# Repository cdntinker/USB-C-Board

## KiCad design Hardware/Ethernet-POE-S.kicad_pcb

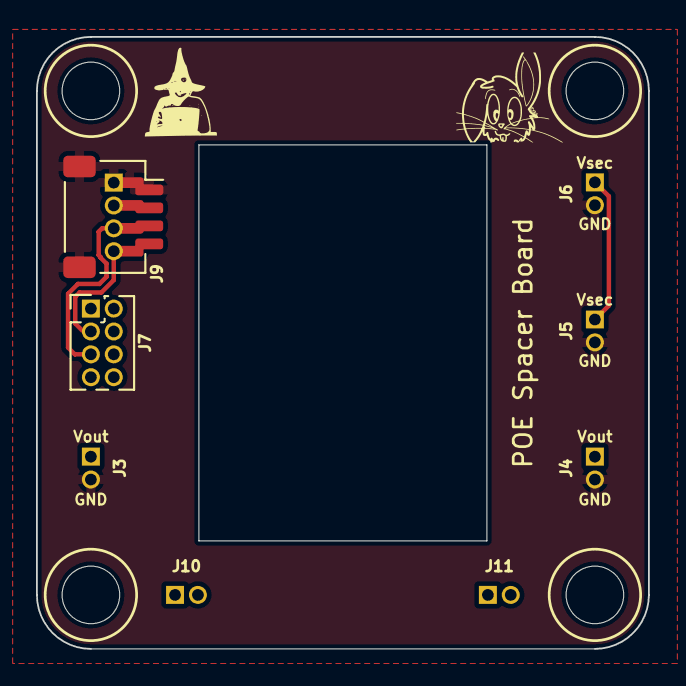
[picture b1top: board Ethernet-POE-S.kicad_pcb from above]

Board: 2 copper layers, 34.0 x 34.0 mm, 8 parts (0 on the bottom side), 4 nets.

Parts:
J3, J4, J5, J6, J10, J11: Conn_01x02_Male; Board_Stacker_2
J7: Conn_01x08_Male; PinHeader_2x04_P1.27mm_Vertical
J9: QWIIC_Stackable; QWIIC_Stack_II

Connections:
GND: J3.2, J4.2, J5.2, J6.2, J9.1, J9.MP (MountPin)
SCL: J7.3, J9.4
SDA: J7.5, J9.3
Vsec: J5.1, J6.1

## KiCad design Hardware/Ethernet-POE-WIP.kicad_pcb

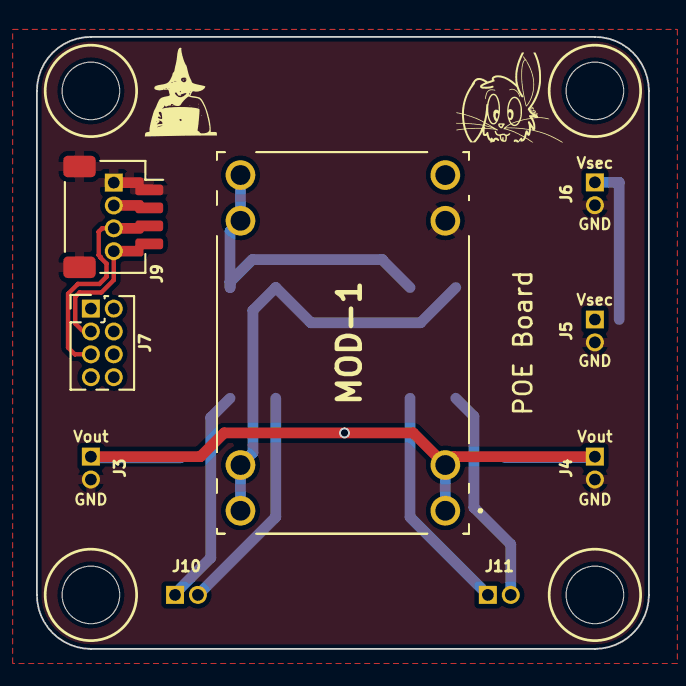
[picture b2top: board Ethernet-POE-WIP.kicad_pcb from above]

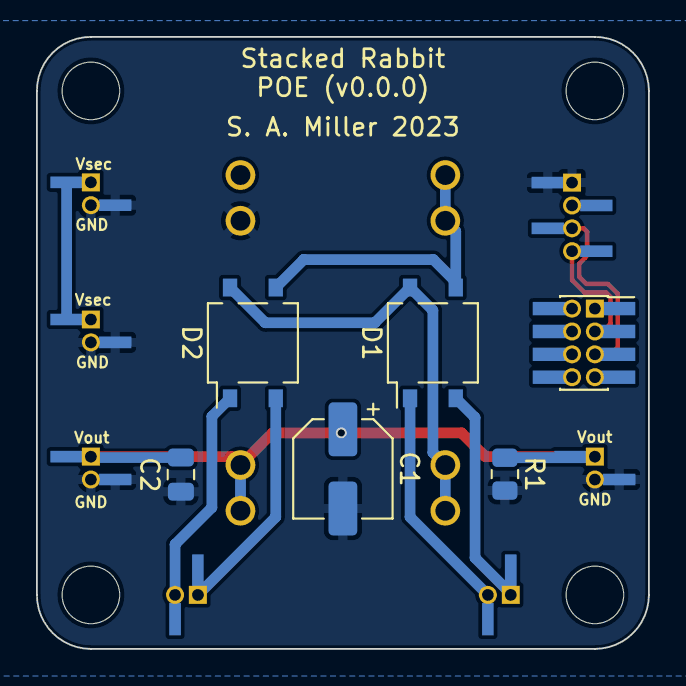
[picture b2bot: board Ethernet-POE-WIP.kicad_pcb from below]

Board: 2 copper layers, 34.0 x 34.0 mm, 14 parts (5 on the bottom side), 11 nets.

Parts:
C1: 100uf; CP_Elec_5x3
C2: 10uf; C_0805_2012Metric
D1, D2: MB4S; TO-269AA
J3, J4, J5, J6, J10, J11: Conn_01x02_Male; Board_Stacker_2
J7: Conn_01x08_Male; PinHeader_2x04_P1.27mm_Vertical
J9: QWIIC_Stackable; QWIIC_Stack_II
MOD-1: Ag9912LP
R1: R; R_0805_2012Metric

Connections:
GND: C1.2, C2.2, J3.2, J4.2, J5.2, J6.2, J9.1, J9.MP (MountPin), MOD-1.3 (-VDC), R1.2
SCL: J7.3, J9.4
SDA: J7.5, J9.3
VA1: D2.2, J11.1
VA2: D2.1, J11.2
VB1: D1.2, J10.1
VB2: D1.1, J10.2
Vin+: D1.3 (+), D2.3 (+), MOD-1.5 (VIN+_1), MOD-1.6 (VIN+_2)
Vin-: D1.4 (-), D2.4 (-), MOD-1.7 (VIN-_1), MOD-1.8 (VIN-_2)
Vout: C1.1, C2.1, J3.1, J4.1, MOD-1.1 (+VDC_1), MOD-1.2 (+VDC_2), R1.1
Vsec: J5.1, J6.1

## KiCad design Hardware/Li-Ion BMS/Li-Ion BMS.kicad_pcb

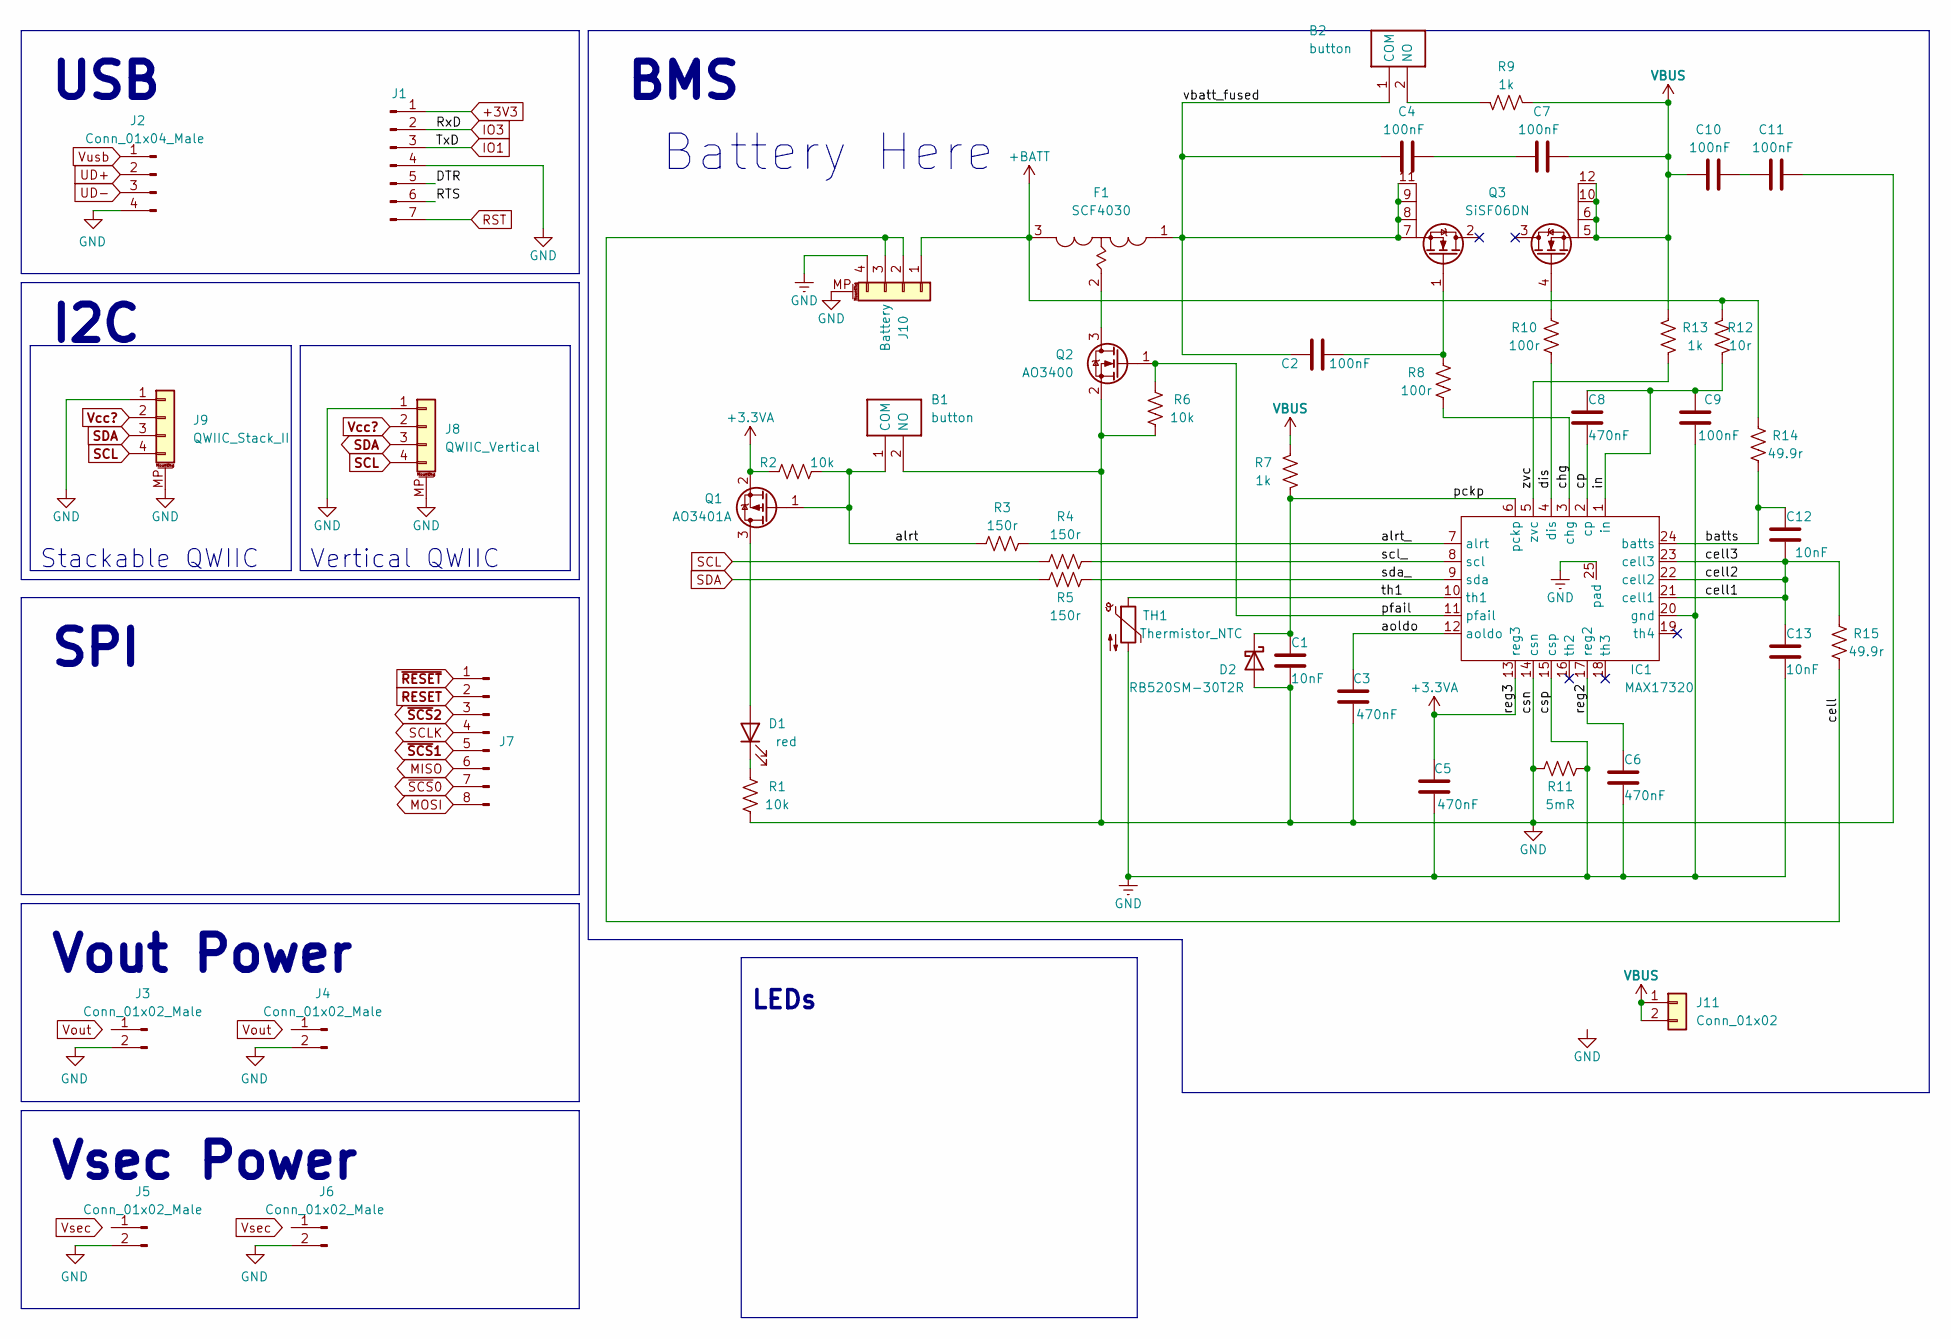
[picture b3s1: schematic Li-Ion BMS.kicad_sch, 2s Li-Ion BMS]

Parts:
B1, B2: button; SW_Push_TS273014TP; LCSC C410373
C1, C12, C13: 10nF; R_0603_1608Metric; LCSC C107059
C2: 100nF; R_0603_1608Metric
C3, C5, C6, C8: 470nF; R_0603_1608Metric; LCSC C1704
C4, C7, C9, C10, C11: 100nF; R_0603_1608Metric; LCSC C83060
D1: red; LED_0603_1608Metric; LCSC C72038
D2: RB520SM-30T2R; D_SOD-523; LCSC C123011
F1: SCF4030; SCF40301204; mouser 504-SCF4030-12-05
IC1: MAX17320; QFN-24-1EP_4x4mm_P0.5mm_EP2.6x2.6mm; mouser 700-MAX17320G20+T
J1: Conn_01x07_Male; Board_Stacker_7
J2: Conn_01x04_Male; Board_Stacker_4; LCSC C2938401 + C2881513
J3, J4, J5, J6: Conn_01x02_Male; Board_Stacker_2; LCSC C2938400 + C2881511
J7: Conn_01x08_Male; PinHeader_2x04_P1.27mm_Vertical; LCSC C2881786 + C2684732
J8: QWIIC_Vertical; LCSC C145961
J9: QWIIC_Stack_II; LCSC C145956 + C2938401 + C2881513
J10: Battery; JST_GH_SM04B-GHS-TB_1x04-1MP_P1.25mm_Horizontal; LCSC C225113
J11: Conn_01x02; PinHeader_1x02_P1.27mm_Vertical
Q1: AO3401A; SOT-23; LCSC C347476
Q2: AO3400; SOT-23; LCSC C20917
Q3: SiSF06DN; SISF06DNT1GE3; mouser 78-SISF06DN-T1-GE3
R1, R2, R6: 10k; R_0603_1608Metric; LCSC C98220
R3, R4, R5: 150r; R_0603_1608Metric; LCSC C22808
R7, R9, R13: 1k; R_0603_1608Metric; LCSC C21190
R8, R10: 100r; R_0603_1608Metric; LCSC C22775
R11: 5mR; R_2512_6332Metric; LCSC C1021512
R12: 10r; R_0603_1608Metric; LCSC C22859
R14, R15: 49.9r; R_0603_1608Metric; LCSC C103679
TH1: Thermistor_NTC; R_0603_1608Metric; LCSC C13564

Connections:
+3.3VA: C5.1, IC1.13 (reg3), Q1.2 (S), R2.1
+BATT: F1.3, J10.1, R12.1, R14.1; also elsewhere on the board
/alrt: B1.1 (COM), Q1.1 (G), R2.2, R3.1
/alrt_: IC1.7 (alrt), R3.2
/aoldo: C3.1, IC1.12 (aoldo)
/chg: IC1.3 (chg), R8.1
/cp: C8.2, IC1.2 (cp)
/dis: IC1.4 (dis), R10.1
/in: C8.1, C9.1, IC1.1 (in), R12.2
/pckp: C1.2, D2.1 (K), IC1.6 (pckp), R7.2
/pfail: IC1.11 (pfail), Q2.1 (G), R6.1
/reg2: C6.1, IC1.17 (reg2)
/scl_: IC1.8 (scl), R4.2
/sda_: IC1.9 (sda), R5.1
/th1: IC1.10 (th1), TH1.1
/vbatt_fused: B2.1 (COM), C2.1, C4.1, F1.1, Q3.7 (S1), Q3.8 (S1), Q3.9 (S1), Q3.11 (S1)
/zvc: IC1.5 (zvc), R13.1
MISO: J7.6
MOSI: J7.8
unnamed: B2.2 (NO), R9.2
unnamed: C2.2, Q3.1 (G1), R8.2
unnamed: C4.2, C7.1
unnamed: C10.2, C11.1
unnamed: D1.1 (K), R1.1
unnamed: D1.2 (A), Q1.3 (D)
unnamed: F1.2, Q2.3 (D)
unnamed: Q3.4 (G2), R10.2
RESET: J7.2
SCL: J8.4, J9.4, R4.1
SCLK: J7.4
SDA: J8.3, J9.3, R5.2
UD+: J2.2
UD-: J2.3
VBUS: C7.2, C10.1, J11.1, J11.2, Q3.5 (S2), Q3.6 (S2), Q3.10 (S2), Q3.12 (S2), R7.1, R9.1, R13.2
Vcc?: J8.2, J9.2
Vusb: J2.1
batts: C12.1, IC1.24 (batts), R14.2
cell: J10.2, J10.3, R15.2; also elsewhere on the board
cell3: C12.2, C13.1, IC1.21 (cell1), IC1.22 (cell2), IC1.23 (cell3), R15.1
~RESET: J7.1
~SCS0: J7.7
~SCS1: J7.5
~SCS2: J7.3

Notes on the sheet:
Vout Power
I2C
Stackable QWIIC
SPI
Vsec Power
USB
Battery Here
Vertical QWIIC
BMS
LEDs

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
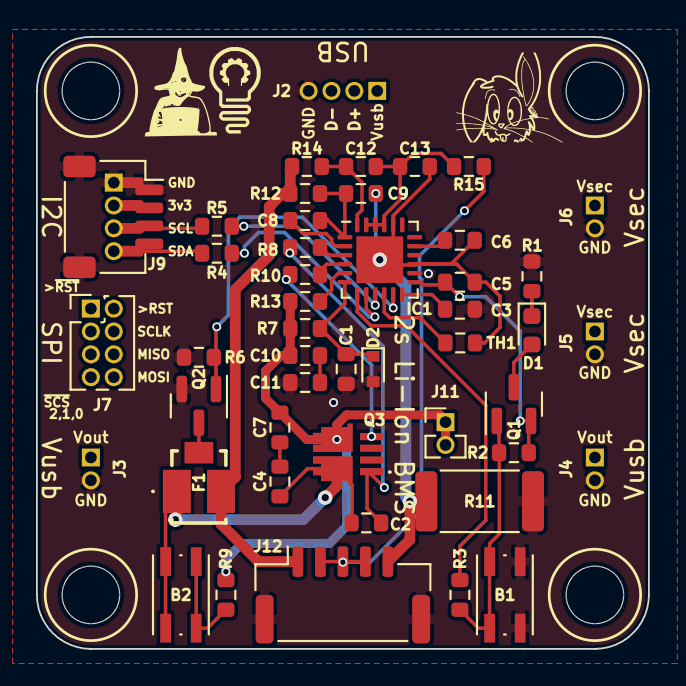
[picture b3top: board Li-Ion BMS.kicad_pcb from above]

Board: 2 copper layers, 34.0 x 34.0 mm, 47 parts (0 on the bottom side), 33 nets.

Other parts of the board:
J12: Conn_01x05_MountingPin; JST_GH_SM05B-GHS-TB_1x05-1MP_P1.25mm_Horizontal

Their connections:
+BATT: J12.1; also elsewhere on the board
cell: J12.2, J12.3, J12.4; also elsewhere on the board

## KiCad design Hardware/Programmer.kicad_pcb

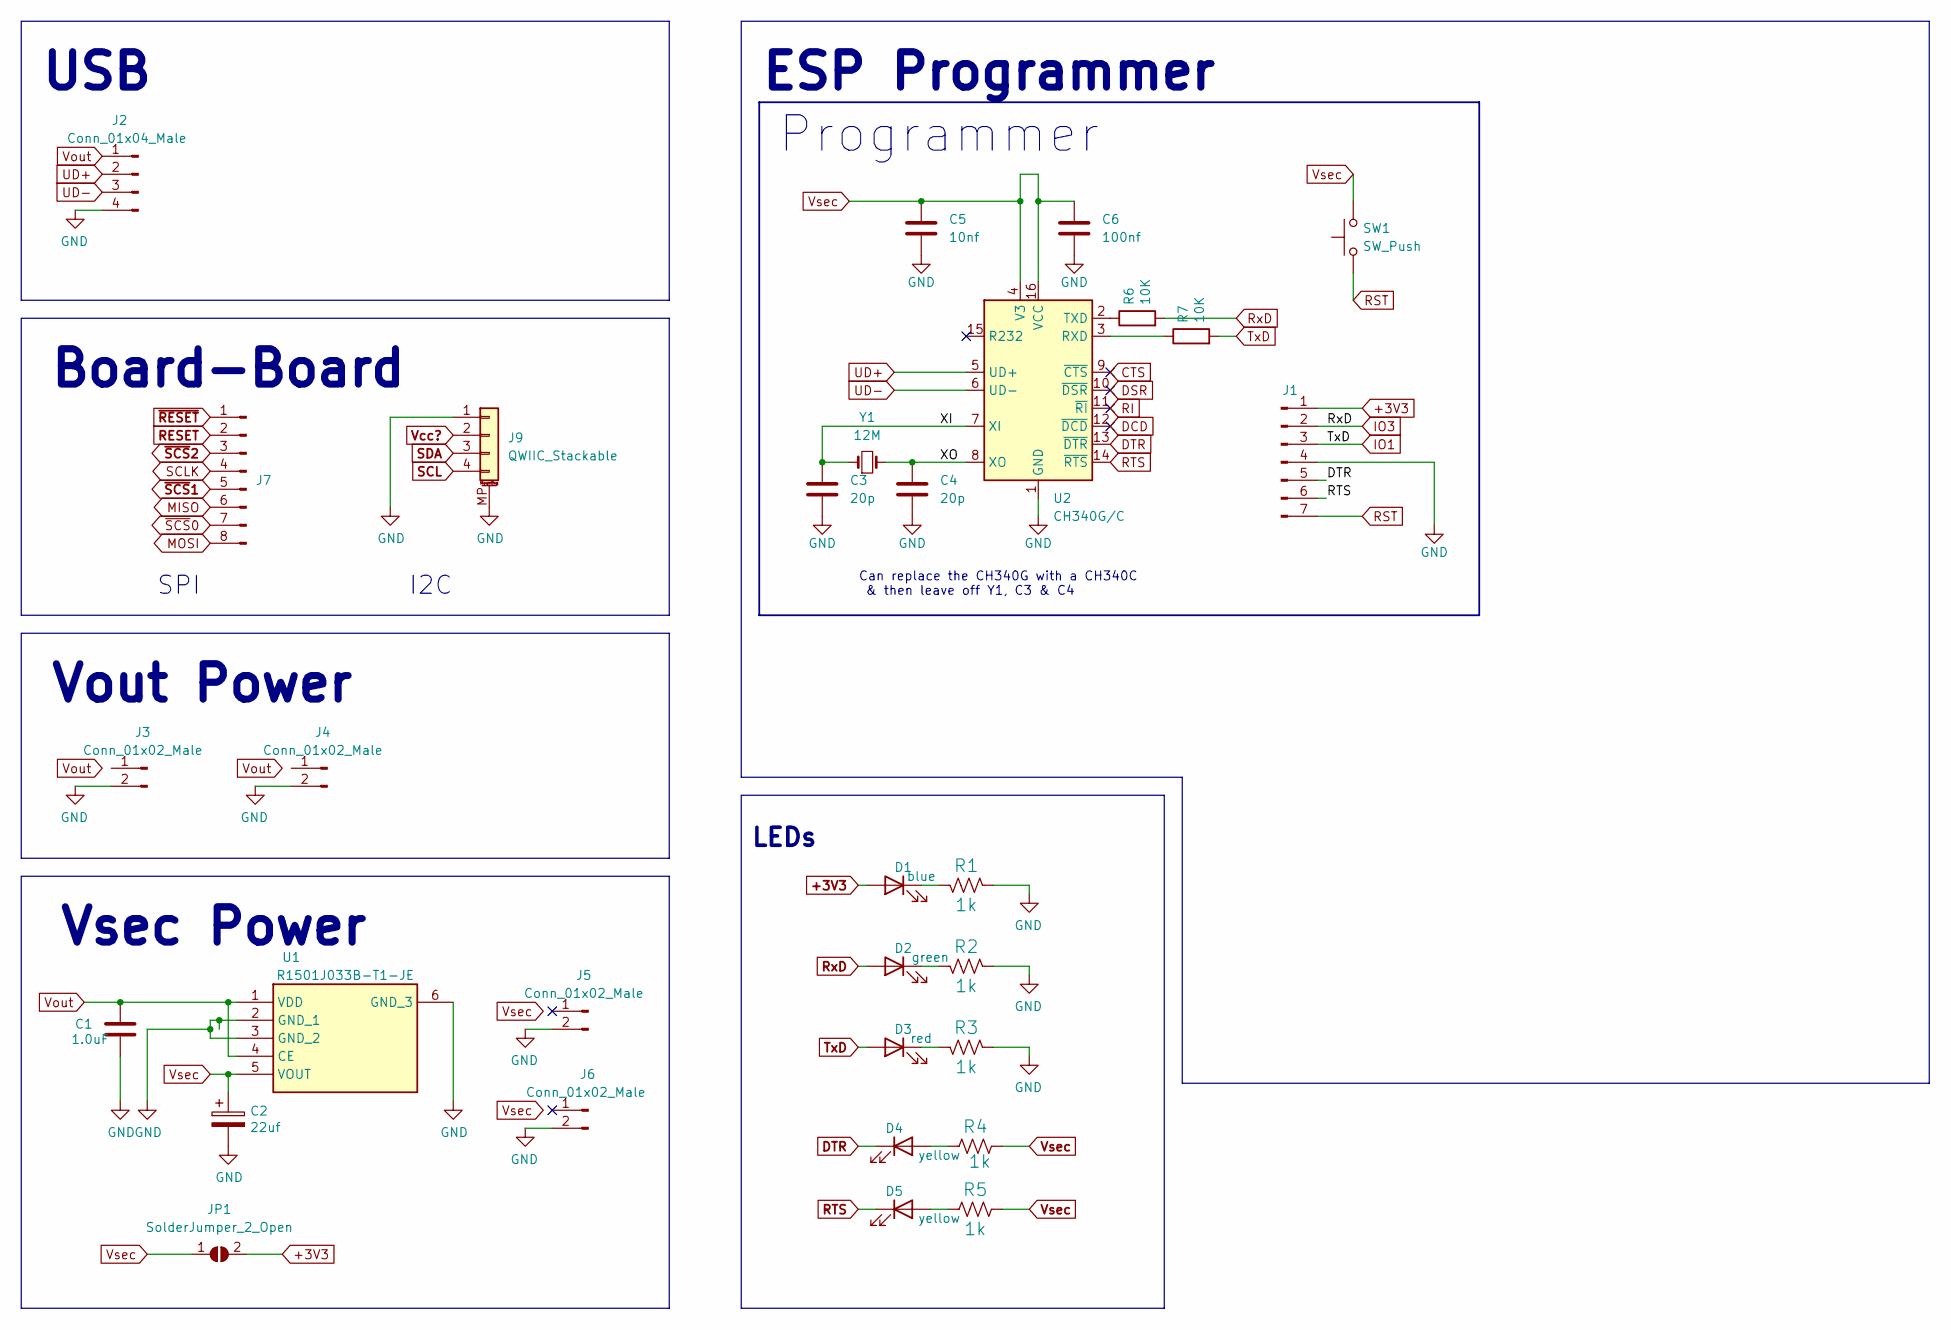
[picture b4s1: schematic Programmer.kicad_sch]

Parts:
C1: 1.0uF; C_0603_1608Metric; LCSC C559769
C2: 22uf; CP_EIA-6032-28-Tantalumm_HandSolder; LCSC C89246
C3, C4: 20p; C_0603_1608Metric_Pad1.08x0.95mm_HandSolder; LCSC C325469
C5: 10nf; C_0603_1608Metric_Pad1.08x0.95mm_HandSolder; LCSC C161232
C6: 100nf; C_0603_1608Metric_Pad1.08x0.95mm_HandSolder; LCSC C235731
D1: blue; LED_0603_1608Metric; LCSC C434420
D2: green; LED_0603_1608Metric; LCSC C434420
D3: red; LED_0603_1608Metric; LCSC C434420
D4: yellow; LED_0603_1608Metric; LCSC C434421
D5: yellow; LED_0603_1608Metric; LCSC C434424
J1: Conn_01x07_Male; Board_Stacker_7
J2: Conn_01x04_Male; Board_Stacker_4
J3, J4, J5, J6: Conn_01x02_Male; Board_Stacker_2
J7: Conn_01x08_Male; PinHeader_2x04_P1.27mm_Vertical; LCSC C2881786 + C2684732
J9: QWIIC_Stackable; QWIIC_Stack_II
JP1: SolderJumper_2_Open; SolderJumper-2_P_Open_Rounded_skinny
R1, R2, R3, R4, R5: 1k; R_0603_1608Metric; LCSC C21190
R6, R7: 10K; R_0603_1608Metric_Pad0.98x0.95mm_HandSolder; LCSC C25804
SW1: SW_Push; SW_Push_TS273014TP; LCSC C2858276
U1: R1501J033B-T1-JE; R1501J033BT1JE; Manufacturer_Part_Number R1501J033B-T1-JE; LCSC C3748149
U2: CH340G/C; SOIC-16_3.9x9.9mm_P1.27mm; LCSC C14267/C84681
Y1: 12M; Crystal_SMD_5032-2Pin_5.0x3.2mm; LCSC C2842275

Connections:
+3V3: D1.2 (A), J1.1, JP1.2 (B)
/XI: C3.1, U2.7 (XI), Y1.1
/XO: C4.1, U2.8 (XO), Y1.2
CTS: U2.9 (~CTS)
DCD: U2.12 (~DCD)
DSR: U2.10 (~DSR)
DTR: D4.1 (K), J1.5, U2.13 (~DTR)
GND: C1.2, C2.2, C3.2, C4.2, C5.2, C6.2, J1.4, J2.4, J3.2, J4.2, J5.2, J6.2, J9.1, J9.MP (MountPin), R1.1, R2.1, R3.1, U1.2 (GND_1), U1.3 (GND_2), U1.6 (GND_3), U2.1 (GND)
IO1: D3.2 (A), J1.3, R7.2
IO3: D2.2 (A), J1.2, R6.2
MISO: J7.6
MOSI: J7.8
unnamed: D1.1 (K), R1.2
unnamed: D2.1 (K), R2.2
unnamed: D3.1 (K), R3.2
unnamed: D4.2 (A), R4.1
unnamed: D5.2 (A), R5.1
unnamed: R6.1, U2.2 (TXD)
unnamed: R7.1, U2.3 (RXD)
RESET: J7.2
RI: U2.11 (~RI)
RST: J1.7, SW1.1
RTS: D5.1 (K), J1.6, U2.14 (~RTS)
SCL: J9.4
SCLK: J7.4
SDA: J9.3
UD+: J2.2, U2.5 (UD+)
UD-: J2.3, U2.6 (UD-)
Vcc?: J9.2
Vout: C1.1, J2.1, U1.1 (VDD), U1.4 (CE)
Vsec: C2.1, C5.1, C6.1, JP1.1 (A), R4.2, R5.2, SW1.2, U1.5 (VOUT), U2.4 (V3), U2.16 (VCC)
~RESET: J7.1
~SCS0: J7.7
~SCS1: J7.5
~SCS2: J7.3

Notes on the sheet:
Vout Power
USB
Programmer
LEDs
Can replace the CH340G with a CH340C & then leave off Y1, C3 & C4
I2C
Board-Board
ESP Programmer
Vsec Power
SPI

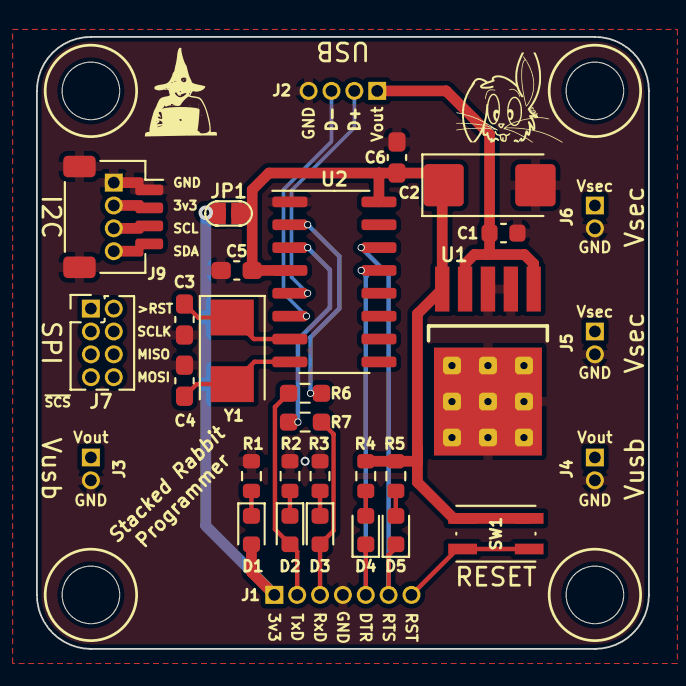
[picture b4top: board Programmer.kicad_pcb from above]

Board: 2 copper layers, 34.0 x 34.0 mm, 31 parts (0 on the bottom side), 20 nets.
